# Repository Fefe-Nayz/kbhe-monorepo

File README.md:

# KBHE

KBHE is a Hall effect keyboard project packaged as one product monorepo: STM32 firmware, the Tauri desktop configurator, the 75HE KiCad PCB, and the mechanical 3D files live together with the documentation needed to build and maintain them.

**CAD: full assembly (v13)**

**Assembled 75% keyboard (pudding caps, RGB)**

## TIPE presentation (synoptic, report, part drawing)

Sourced materials for the TIPE deliverables: synoptic, English summary, part naming drawing, a short workbench video clip.

- [tipe-synoptique.pdf](assets/presentation/tipe-synoptique.pdf) — project synoptic
- [tipe-english-paper.pdf](assets/presentation/tipe-english-paper.pdf) — short English paper
- [tipe-drawing-part-labels.pdf](assets/presentation/tipe-drawing-part-labels.pdf) — drawing, part / reference labels
- [tipe-bench-clip.mp4](assets/presentation/tipe-bench-clip.mp4) — short bench / lab clip

## 75HE v1.0 main PCB (photographs)

| Top: switches + per-key RGB | Bottom: solder side (hand) |
| --- | --- |
|  |  |

## Final 75HE PCB (full board, KiCad 3D)

Renders of the main production board, exported from the KiCad project in `hardware/pcb/75he/Assets/`.

| Top (component side) | Bottom (solder side) |
| --- | --- |
|  |  |

## Prototyping: fabrication, plates, 3D prints

| Metal plate and 3D-printed top bezel | FDM: case half on the build plate | Printed set: top bezel, switch plate, bottom (75HE embossed) |
| --- | --- | --- |
|  |  |  |

## STM32 breakout, hall prototypes, and TIPE v0.1 bench setup

| STM32 test PCB: STLink + DFU silk | STM32: USB-C, DFU area (top) | STM32: bench, USB-C, DFU + flying wires |
| --- | --- | --- |
|  |  |  |

| 6-key Hall bench PCB | **TIPE Keyboard HE** v0.1 (CD74HC4067) — bench wiring | v0.1 Hall analog board **cabled to** STM32 breakout |
| --- | --- | --- |
|  |  |  |

## TIPE research bench and lab (wide stills)

| At the bench (1) | At the bench (2) | At the bench (3) |
| --- | --- | --- |
|  |  |  |

## First-time installation

Follow the instructions in [docs/firmware/INSTALLATION.md](docs/firmware/INSTALLATION.md) to flash the firmware for the first time using STM32CubeProgrammer.

<!-- ## First-time board programming (STM32CubeProgrammer, DFU)

The **first** time you program a **blank** board you need a Release build, the physical **DFU / FS** switch, **ROM DFU** over USB, and **STM32CubeProgrammer** to erase the chip and program the custom bootloader and application image. Ongoing updates use the Tauri app or the RAW HID tools instead.

**Step-by-step (French):** [docs/firmware/overview.md](docs/firmware/overview.md) — start at the section *Flash initial d'une carte neuve (bootloader custom)* (build → DFU connect → full erase → flash `kbhe_bootloader.hex` at `0x08000000` and `kbhe.hex` at `0x08010000` → normal boot → optional `raw_hid.py --flash` to finalize the updater). Related notes: [docs/firmware/raw_hid_usage.md](docs/firmware/raw_hid_usage.md), [docs/README.md](docs/README.md). -->

## Updating firmware

Follow the instructions in [docs/firmware/INSTALLATION.md](docs/firmware/INSTALLATION.md) to update the firmware using the Configurator app or STM32CubeProgrammer.

## Repository Layout

- `firmware/` - STM32F723 firmware, custom RAW HID bootloader, CMake toolchain and CubeMX-generated support files.
- `apps/configurator/` - Tauri desktop configurator for key settings, calibration, lighting, firmware flashing and app updates.
- `integrations/libhmk/` - pinned KBHE libhmk fork, portable RGB/HID protocol client, and reproducible upstream patch mirror.
- `hardware/pcb/75he/` - KiCad PCB project with project-local libraries, 3D models, documentation and legacy PCB revisions.
- `hardware/3d/` - mechanical source files and exported models. Large mechanical formats are tracked with Git LFS.
- `assets/presentation/` - TIPE PDFs (synoptic, English paper, part-label drawing) and a short workbench **.mp4** clip.
- `assets/cad/75he-mechanical/` - mechanical **CAD** stills: full assembly, shaded exploded stack, isometric, part-exploded **top / bottom / three-quarter** views.
- `assets/photos/` - real photos, grouped by topic: `product/`, `pcb-75he/`, `pcb-mcu-breakout/`, `prototypes/`, `fdm-fabrication/`, `tipe-lab/`, `app/`. No camera timestamps in file names: names describe **content**.
- `tools/`, `docs/`, `layouts/`, `data/` - as before.

## Firmware

```powershell
cmake --preset Release
cmake --build --preset Release
```

Artifacts are written to `build/Release/`. The CI also builds `Release-apponly` for app-only firmware packages. For a **first** flash of blank hardware, follow [docs/firmware/overview.md](docs/firmware/overview.md) (DFU, STM32CubeProgrammer) before relying on the app’s HID updater.

## Configurator

The desktop app communicates with the keyboard over RAW HID to handle keymap, performance, gamepad mode, calibration, the rotary encoder, lighting, and firmware updates. Example: **Keymap** for a 75% **ISO-FR** layout in dark UI.

```powershell
cd apps/configurator
bun install
bun run build
cd src-tauri
cargo check --locked
```

For a local installer build:

```powershell
cd apps/configurator
bun tauri build
```

## Releases

The monorepo uses explicit tag prefixes so the desktop app can distinguish app installers from firmware binaries:

- `firmware-vX.Y.Z` builds firmware artifacts and publishes them in a GitHub Release.
- `app-vX.Y.Z` builds the Tauri installer and publishes it in a GitHub Release.

The configurator checks these release streams from inside the app. App updates download and launch the published installer. Firmware updates download the latest firmware binary and flash it through the existing RAW HID update path.

## Working With 3D Assets

Install Git LFS before cloning or pushing mechanical changes:

```powershell
git lfs install
```

The current mechanical files are under `hardware/3d/current/`; older exports are kept under `hardware/3d/legacy/`.

## Mechanical CAD: exploded part views and overviews

Files live in `assets/cad/75he-mechanical/`. The **“parts”** set are consistent orientations of the decomposed case + plate; **“legacy”** older exports use different camera framing.

| Exploded: parts from top | Exploded: parts, bottom / rear | Exploded: three-quarter (right) |
| --- | --- | --- |
|  |  |  |

| All layers **stacked** (shade) | Full keyboard **3/4** (no case explode) | **Side elevation** (older export) | **Rear-left** isometric (older export) |
| --- | --- | --- | --- |
|  |  |  |  |

### Legacy KiCad prototypes (3D exports from the repo)

| 6-key Hall | MCU v1 | MCU v2 |
| --- | --- | --- |
|  |  |  |

## Current limitations - TODOs
- For transparent keycaps the space bar lacks leds on the sides
- For the enter key the led is colliding with the stabilizer which needs to be cut
- DFU switch should be hidden
- Wireless version
- Underglow
- Reversed mounted LEDs (single side pcb)
- Mountiing holes placements may need to be adjusted
- Try lowering pcb layer count without sacrificing noise performance
- Add support for libhmk
- Final touches on 3D models: adjust tolerances, raise the top case, adjust USB and switch hole position

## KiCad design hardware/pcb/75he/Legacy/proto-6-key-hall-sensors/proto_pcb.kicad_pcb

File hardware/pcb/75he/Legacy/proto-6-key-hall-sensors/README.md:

# Proto 6-Key Hall Sensors

Six-key prototype used to validate the hall-effect sensing approach only.

This board has no MCU and no keyboard logic. Its local `Library/` and `Docs/` folders are intentionally vendored so the project can be opened independently from the root PCB.

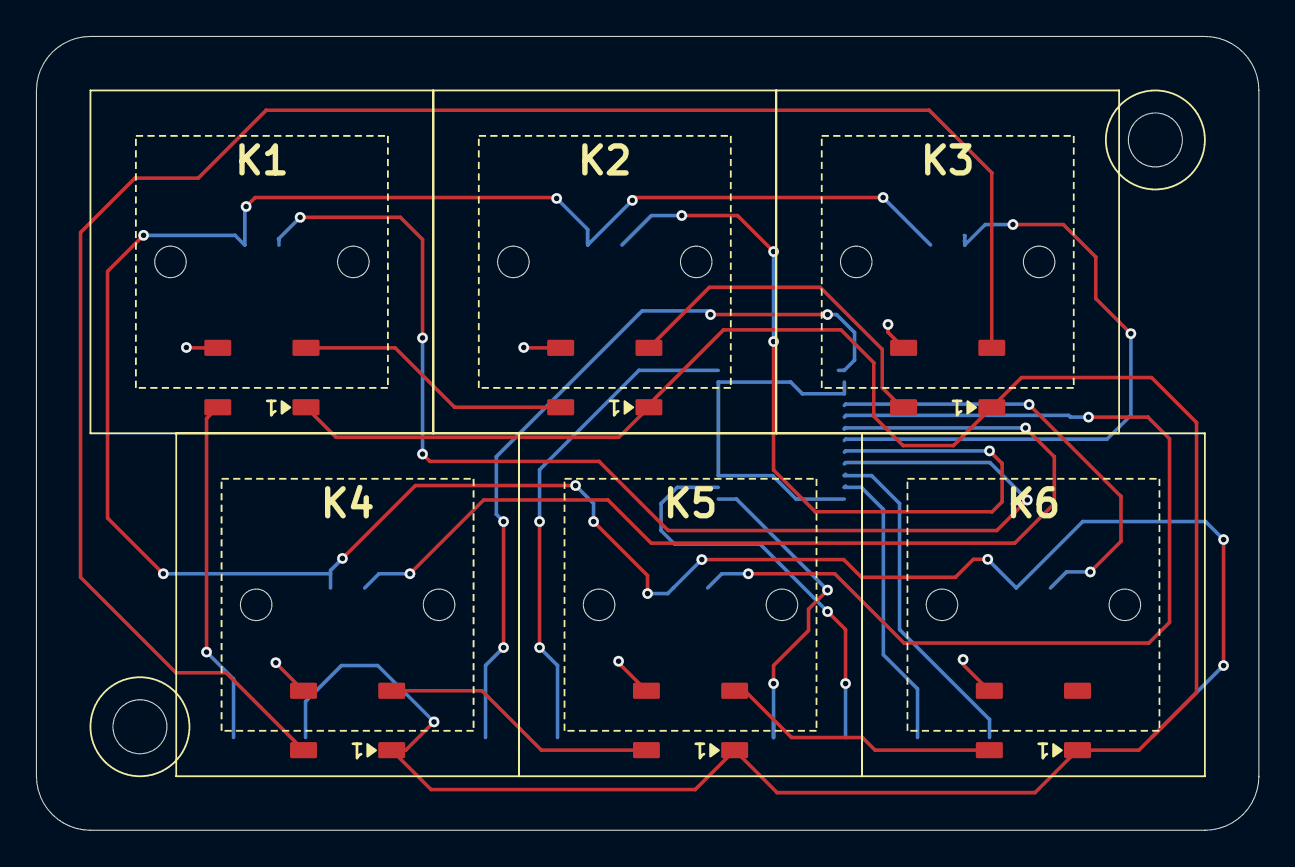
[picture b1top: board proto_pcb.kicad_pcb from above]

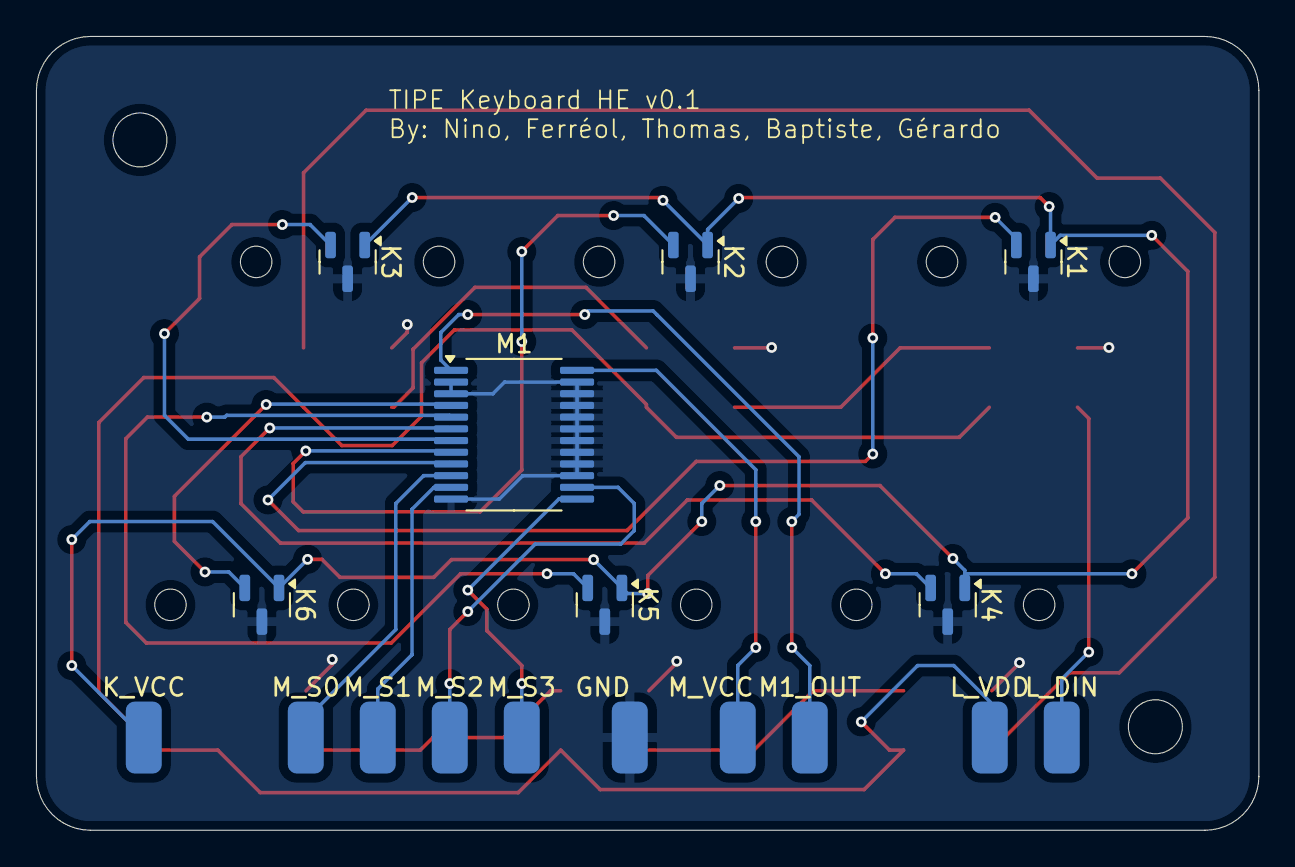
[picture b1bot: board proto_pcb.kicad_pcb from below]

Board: 2 copper layers, 67.9 x 44.1 mm, 23 parts (17 on the bottom side), 21 nets.

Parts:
GND: SolderWirePad_1x01_SMD_2x4mm
K1, K2, K3, K4, K5, K6: DRV5055A4QDBZR; SOT-23
K_VCC: SolderWirePad_1x01_SMD_2x4mm
L1, L2, L3, L4, L5, L6: XL-5050RGBC-2812B-S; LED_WS2812B_PLCC4_5.0x5.0mm_P3.2mm
L_DIN: SolderWirePad_1x01_SMD_2x4mm
L_VDD: SolderWirePad_1x01_SMD_2x4mm
M1: CD74HC4067SM96; SSOP-24_5.3x8.2mm_P0.65mm
M1_OUT: SolderWirePad_1x01_SMD_2x4mm
M_S0, M_S1, M_S2, M_S3: SolderWirePad_1x01_SMD_2x4mm
M_VCC: SolderWirePad_1x01_SMD_2x4mm

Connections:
GND: GND.10, K1.3 (GND), K2.3 (GND), K3.3 (GND), K4.3 (GND), K5.3 (GND), K6.3 (GND), L1.3 (VSS), L2.3 (VSS), L3.3 (VSS), L4.3 (VSS), L5.3 (VSS), L6.3 (VSS), M1.2 (I7), M1.3 (I6), M1.12 (GND), M1.15 (~E), M1.16 (I15), M1.17 (I14), M1.18 (I13), M1.19 (I12), M1.20 (I11), M1.21 (I10), M1.22 (I9), M1.23 (I8)
K1_OUT: K1.2 (OUT), M1.9 (I0)
K2_OUT: K2.2 (OUT), M1.8 (I1)
K3_OUT: K3.2 (OUT), M1.7 (I2)
K4_OUT: K4.2 (OUT), M1.6 (I3)
K5_OUT: K5.2 (OUT), M1.5 (I4)
K6_OUT: K6.2 (OUT), M1.4 (I5)
K_VCC: K1.1 (VCC), K2.1 (VCC), K3.1 (VCC), K4.1 (VCC), K5.1 (VCC), K6.1 (VCC), K_VCC.8
L_DIN: L1.4 (DIN), L_DIN.5
L_VDD: L1.1 (VDD), L2.1 (VDD), L3.1 (VDD), L4.1 (VDD), L5.1 (VDD), L6.1 (VDD), L_VDD.9
M1_OUT: M1.1 (COM), M1_OUT.6
M_S0: M1.10 (S0), M_S0.1
M_S1: M1.11 (S1), M_S1.2
M_S2: M1.14 (S2), M_S2.3
M_S3: M1.13 (S3), M_S3.4
M_VCC: M1.24 (VCC), M_VCC.7
unnamed: L1.2 (DOUT), L2.4 (DIN)
unnamed: L2.2 (DOUT), L3.4 (DIN)
unnamed: L3.2 (DOUT), L4.4 (DIN)
unnamed: L4.2 (DOUT), L5.4 (DIN)
unnamed: L5.2 (DOUT), L6.4 (DIN)

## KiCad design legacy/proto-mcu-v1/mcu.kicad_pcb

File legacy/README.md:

# Legacy PCB Revisions

This folder keeps older KiCad project revisions as source-only archives.

Generated outputs, backups, fabrication packages, render exports, footprint caches, and local KiCad UI state were intentionally removed. The projects keep their KiCad sources and required local libraries, with external 3D model references rewritten to repository-local paths where available.

Each legacy project keeps KiCad project files at its root and stores project-local libraries under `Library/`:

- `Library/Footprints`
- `Library/Symbols`
- `Library/3D`

Projects:

- `mcu-2025-11-18`: MCU board revision from `hall-effect-keyboard/mcu-final/mcu-2025-11-18_230059`.
- `mcu-2025-11-18-04f0a440`: MCU board revision from the downloaded `hall-effect-keyboard-04f0a440...` archive.
- `proto-pcb`: prototype PCB revisions from `hall-effect-keyboard/proto_pcb`.

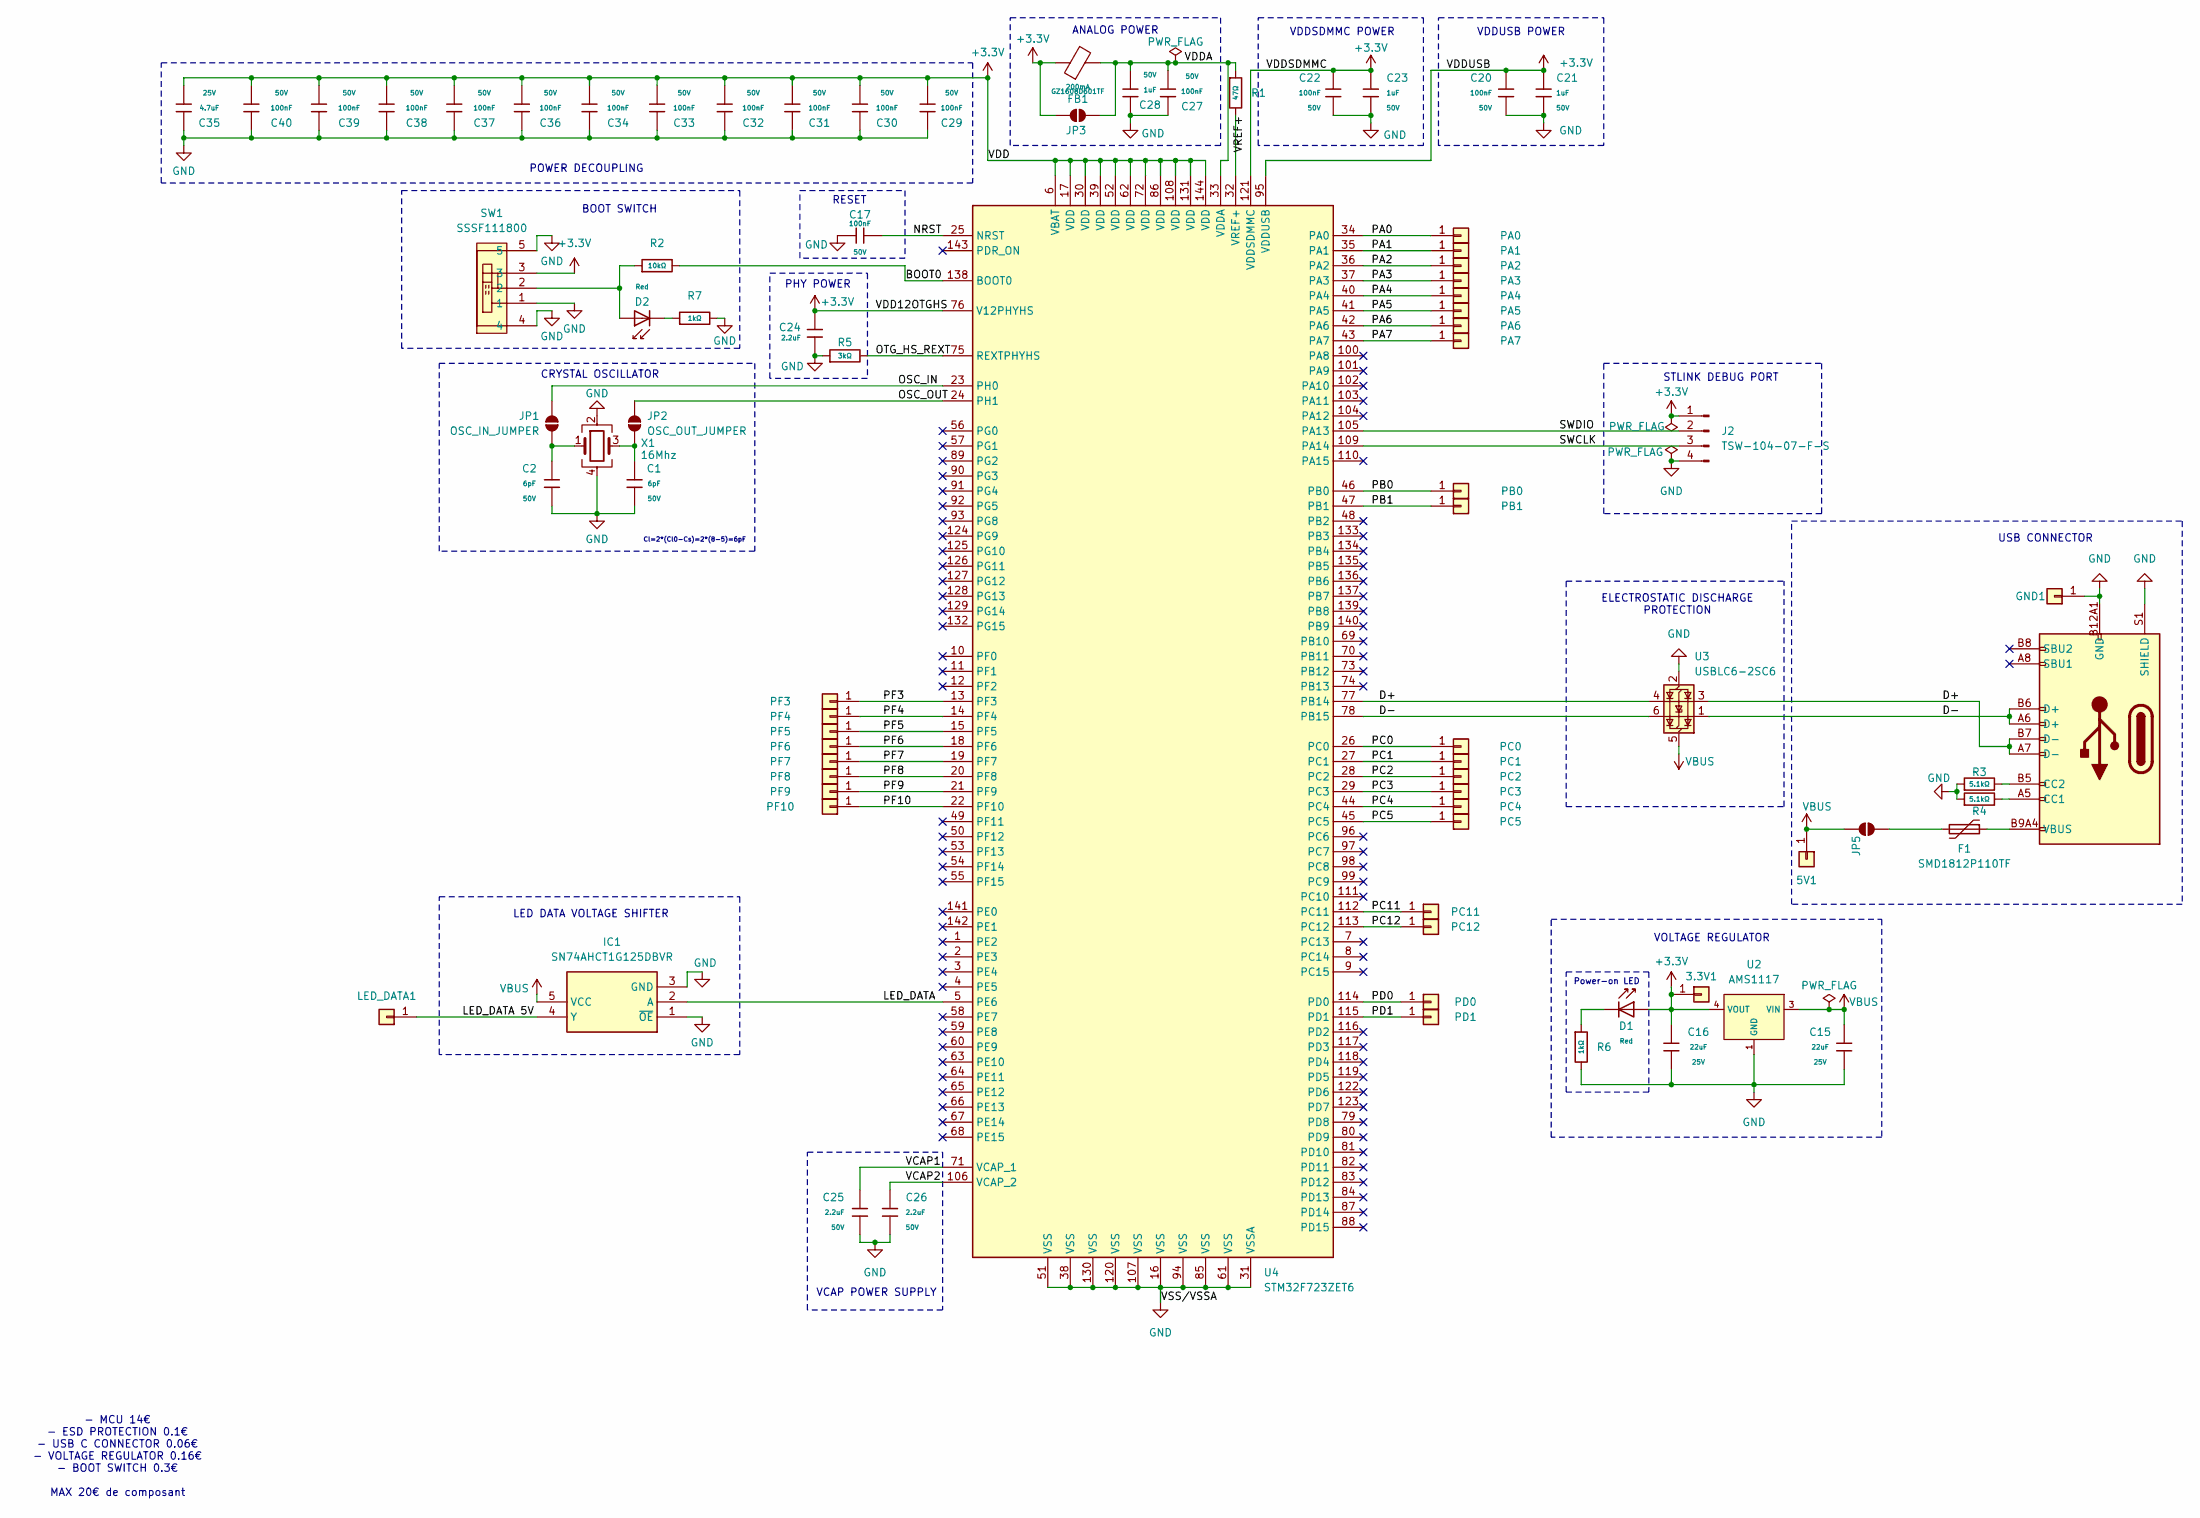
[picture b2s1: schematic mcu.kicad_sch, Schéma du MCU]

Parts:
3.3V1, 5V1: Conn_01x01; SolderWirePad_1x01_SMD_2x4mm
C1, C2: 6pF; C_0603; Voltage Rated 50V; Tolerance ±5%; Part CL10C100JB8NNNC; LCSC C1634
C15, C16: 22uF; C_0805; Voltage Rated 25V; Tolerance ±20%; Part CL21A226MAQNNNE; LCSC C45783
C17, C20, C22, C27, C29, C30, C31, C32, C33, C34, C36, C37, C38, C39, C40: 100nF; C_0603; Voltage Rated 50V; Tolerance ±10%; Part CC0603KRX7R9BB104; LCSC C14663
C21, C23, C28: 1uF; C_0805; Voltage Rated 50V; Tolerance ±10%; Part CL21B105KBFNNNE; LCSC C28323
C24, C25, C26: 2.2uF; C_0805; Voltage Rated 50V; Tolerance ±10%; Part CL21A225KBQNNNE; LCSC C377773
C35: 4.7uF; C_0805; Voltage Rated 25V; Tolerance ±10%; Part CL21A475KAQNNNE; LCSC C1779
D1, D2: Red; D_0603; Part KT-0603R; LCSC C2286
F1: SMD1812P110TF; Fuse_1812_4532Metric; LCSC C3102
FB1: GZ1608D601TF; FB_0603; Current Rating 200mA; Tolerance ±25%; Part GZ1608D601TF; LCSC C1002
GND1: Conn_01x01; SolderWirePad_1x01_SMD_2x4mm
IC1: SN74AHCT1G125DBVR; SOT95P280X145-5N; Manufacturer_Part_Number SN74AHCT1G125DBVR; Mouser Part Number 595-SNAHCT1G125DBVR
J1: Connector, USB-TYPE-C-16P; TYPE-C-SMD_HX-TYPE-C-16PIN; LCSC C2927039
J2: TSW-104-07-F-S; PinHeader_1x04_P2.54mm_Vertical; LCSC C3329057
JP1: OSC_IN_JUMPER; SolderJumper-2_P1.3mm_Open_RoundedPad1.0x1.5mm
JP2: OSC_OUT_JUMPER; SolderJumper-2_P1.3mm_Open_RoundedPad1.0x1.5mm
JP3: FERRITE_IN_JUMP; SolderJumper-2_P1.3mm_Open_RoundedPad1.0x1.5mm
JP5: VBUS_JP; SolderJumper-2_P1.3mm_Open_RoundedPad1.0x1.5mm
LED_DATA1: Conn_01x01; SolderWirePad_1x01_SMD_2x4mm
PA0, PA1, PA2, PA3, PA4, PA5, PA6, PA7: Conn_01x01; SolderWirePad_1x01_SMD_2x4mm
PB0, PB1: Conn_01x01; SolderWirePad_1x01_SMD_2x4mm
PC0, PC1, PC2, PC3, PC4, PC5, PC11, PC12: Conn_01x01; SolderWirePad_1x01_SMD_2x4mm
PD0, PD1: Conn_01x01; SolderWirePad_1x01_SMD_2x4mm
PF3, PF4, PF5, PF6, PF7, PF8, PF9, PF10: Conn_01x01; SolderWirePad_1x01_SMD_2x4mm
R1: 47Ω; R_0402; Overload Voltage (Max) 50V; Tolerance ±1%; Part 0402WGF470JTCE; LCSC C25118
R2: 10kΩ; R_0402; Overload Voltage (Max) 50V; Tolerance ±1%; Part 0402WGF1002TCE; LCSC C25744
R3, R4: 5.1kΩ; R_0402; Overload Voltage (Max) 50V; Tolerance ±1%; Part 0402WGF5101TCE; LCSC C25905
R5: 3kΩ; R_0805; Overload Voltage (Max) 150V; Tolerance ±1%; Part 0805W8F3001T5E; LCSC C17661
R6, R7: 1kΩ; R_0402; Overload Voltage (Max) 50V; Tolerance ±1%; Part 0402WGF1001TCE; LCSC C11702
SW1: SSSF111800; SW-TH_SSSF111800; LCSC Part C97450
U2: AMS1117; SOT-223-3_L6.5-W3.4-P2.30-LS7.0-BR; Output Voltage 3.3V; Dropout Voltage 1.3V@(800mA); Part AMS1117-3.3; LCSC C6186
U3: USBLC6-2SC6; SOT-23-6; LCSC C7519
U4: STM32F723ZET6; LQFP-144_20x20mm_P0.5mm; LCSC C1340305
X1: 16Mhz; Crystal_SMD_2520-4Pin_2.5x2.0mm; LCSC C280836

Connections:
+3.3V: 3.3V1.1, C16.1, C20.1, C21.2, C22.1, C23.2, C24.1, C29.1, C30.1, C31.1, C32.1, C33.1, C34.1, C35.1, C36.1, C37.1, C38.1, C39.1, C40.1, D1.2, FB1.1, J2.1, JP3.1 (A), SW1.3, U2.2 (VOUT), U2.4 (VOUT), U4.6 (VBAT), U4.17 (VDD), U4.30 (VDD), U4.39 (VDD), U4.52 (VDD), U4.62 (VDD), U4.72 (VDD), U4.76 (V12PHYHS), U4.86 (VDD), U4.95 (VDDUSB), U4.108 (VDD), U4.121 (VDDSDMMC), U4.131 (VDD), U4.144 (VDD)
/BOOT0: R2.2, U4.138 (BOOT0)
/D+: J1.A7 (D-), J1.B7 (D-), U3.3 (I/O2), U3.4 (I/O2), U4.77 (PB14)
/D-: J1.A6 (D+), J1.B6 (D+), U3.1 (I/O1), U3.6 (I/O1), U4.78 (PB15)
/LED_DATA: IC1.2 (A), U4.5 (PE6)
/LED_DATA 5V: IC1.4 (Y), LED_DATA1.1
/NRST: C17.1, U4.25 (NRST)
/OSC_IN: JP1.1 (A), U4.23 (PH0)
/OSC_OUT: JP2.2 (B), U4.24 (PH1)
/OTG_HS_REXT: R5.2, U4.75 (REXTPHYHS)
/PA0: PA0.1, U4.34 (PA0)
/PA1: PA1.1, U4.35 (PA1)
/PA2: PA2.1, U4.36 (PA2)
/PA3: PA3.1, U4.37 (PA3)
/PA4: PA4.1, U4.40 (PA4)
/PA5: PA5.1, U4.41 (PA5)
/PA6: PA6.1, U4.42 (PA6)
/PA7: PA7.1, U4.43 (PA7)
/PB0: PB0.1, U4.46 (PB0)
/PB1: PB1.1, U4.47 (PB1)
/PC0: PC0.1, U4.26 (PC0)
/PC1: PC1.1, U4.27 (PC1)
/PC2: PC2.1, U4.28 (PC2)
/PC3: PC3.1, U4.29 (PC3)
/PC4: PC4.1, U4.44 (PC4)
/PC5: PC5.1, U4.45 (PC5)
/PC11: PC11.1, U4.112 (PC11)
/PC12: PC12.1, U4.113 (PC12)
/PD0: PD0.1, U4.114 (PD0)
/PD1: PD1.1, U4.115 (PD1)
/PF3: PF3.1, U4.13 (PF3)
/PF4: PF4.1, U4.14 (PF4)
/PF5: PF5.1, U4.15 (PF5)
/PF6: PF6.1, U4.18 (PF6)
/PF7: PF7.1, U4.19 (PF7)
/PF8: PF8.1, U4.20 (PF8)
/PF9: PF9.1, U4.21 (PF9)
/PF10: PF10.1, U4.22 (PF10)
/SWCLK: J2.3, U4.109 (PA14)
/SWDIO: J2.2, U4.105 (PA13)
/VCAP1: C25.2, U4.71 (VCAP_1)
/VCAP2: C26.2, U4.106 (VCAP_2)
/VDDA: C27.1, C28.1, FB1.2, JP3.2 (B), R1.1, U4.33 (VDDA)
/VREF+: R1.2, U4.32 (VREF+)
GND: C1.2, C2.2, C15.2, C16.2, C17.2, C20.2, C21.1, C22.2, C23.1, C24.2, C25.1, C26.1, C27.2, C28.2, C29.2, C30.2, C31.2, C32.2, C33.2, C34.2, C35.2, C36.2, C37.2, C38.2, C39.2, C40.2, GND1.1, IC1.1 (~OE), IC1.3 (GND), J1.A12B1 (GND), J1.B12A1 (GND), J1.S1 (SHIELD), J2.4, R3.1, R4.1, R5.1, R6.2, R7.2, SW1.1, SW1.4, SW1.5, U2.1 (GND), U3.2 (GND), U4.16 (VSS), U4.31 (VSSA), U4.38 (VSS), U4.51 (VSS), U4.61 (VSS), U4.85 (VSS), U4.94 (VSS), U4.107 (VSS), U4.120 (VSS), U4.130 (VSS), X1.2, X1.4
unnamed: D1.1, R6.1
unnamed: D2.1, R7.1
unnamed: D2.2, R2.1, SW1.2
unnamed: F1.1, J1.A9B4 (VBUS), J1.B9A4 (VBUS)
unnamed: J1.A5 (CC1), R4.2
unnamed: J1.B5 (CC2), R3.2
unnamed: C2.1, JP1.2 (B), X1.1
unnamed: C1.1, JP2.1 (A), X1.3
unnamed: F1.2, JP5.2 (B)
VBUS: 5V1.1, C15.1, IC1.5 (VCC), JP5.1 (A), U2.3 (VIN), U3.5 (VBUS)

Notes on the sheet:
STLINK DEBUG PORT
VDDSDMMC POWER
PHY POWER
LED DATA VOLTAGE SHIFTER
USB CONNECTOR
VCAP POWER SUPPLY
ELECTROSTATIC DISCHARGE PROTECTION
VOLTAGE REGULATOR
POWER DECOUPLING
Cl=2*(Cl0-Cs)=2*(8-5)=6pF
Power-on LED
- MCU 14€ - ESD PROTECTION 0.1€ - USB C CONNECTOR 0.06€ - VOLTAGE REGULATOR 0.16€ - BOOT SWITCH 0.3€ MAX 20€ de composant
BOOT SWITCH
CRYSTAL OSCILLATOR
ANALOG POWER
RESET
VDDUSB POWER

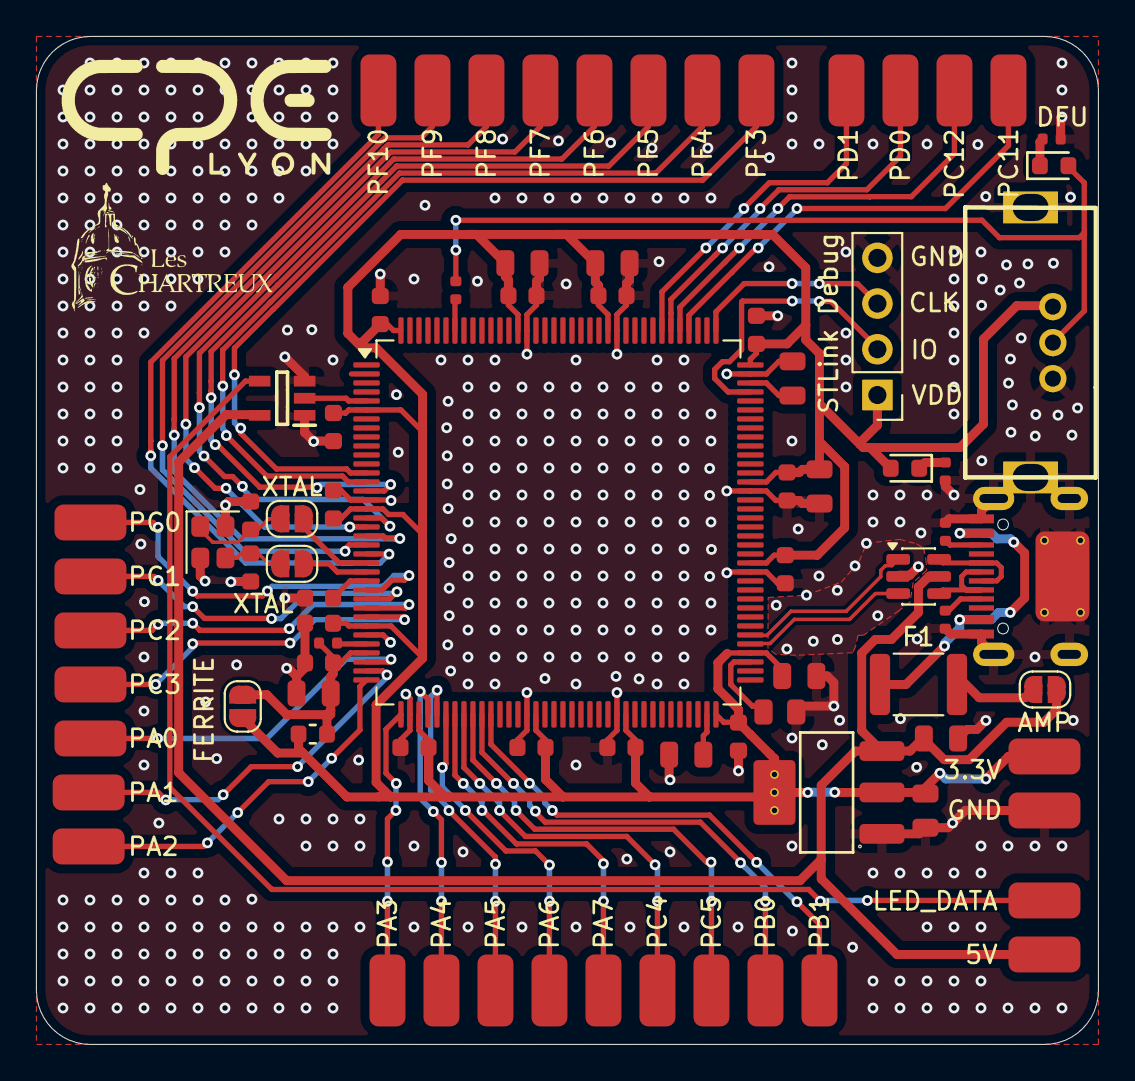
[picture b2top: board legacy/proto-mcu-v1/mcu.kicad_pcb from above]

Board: 2 copper layers, 59.0 x 56.0 mm, 81 parts (0 on the bottom side), 55 nets.

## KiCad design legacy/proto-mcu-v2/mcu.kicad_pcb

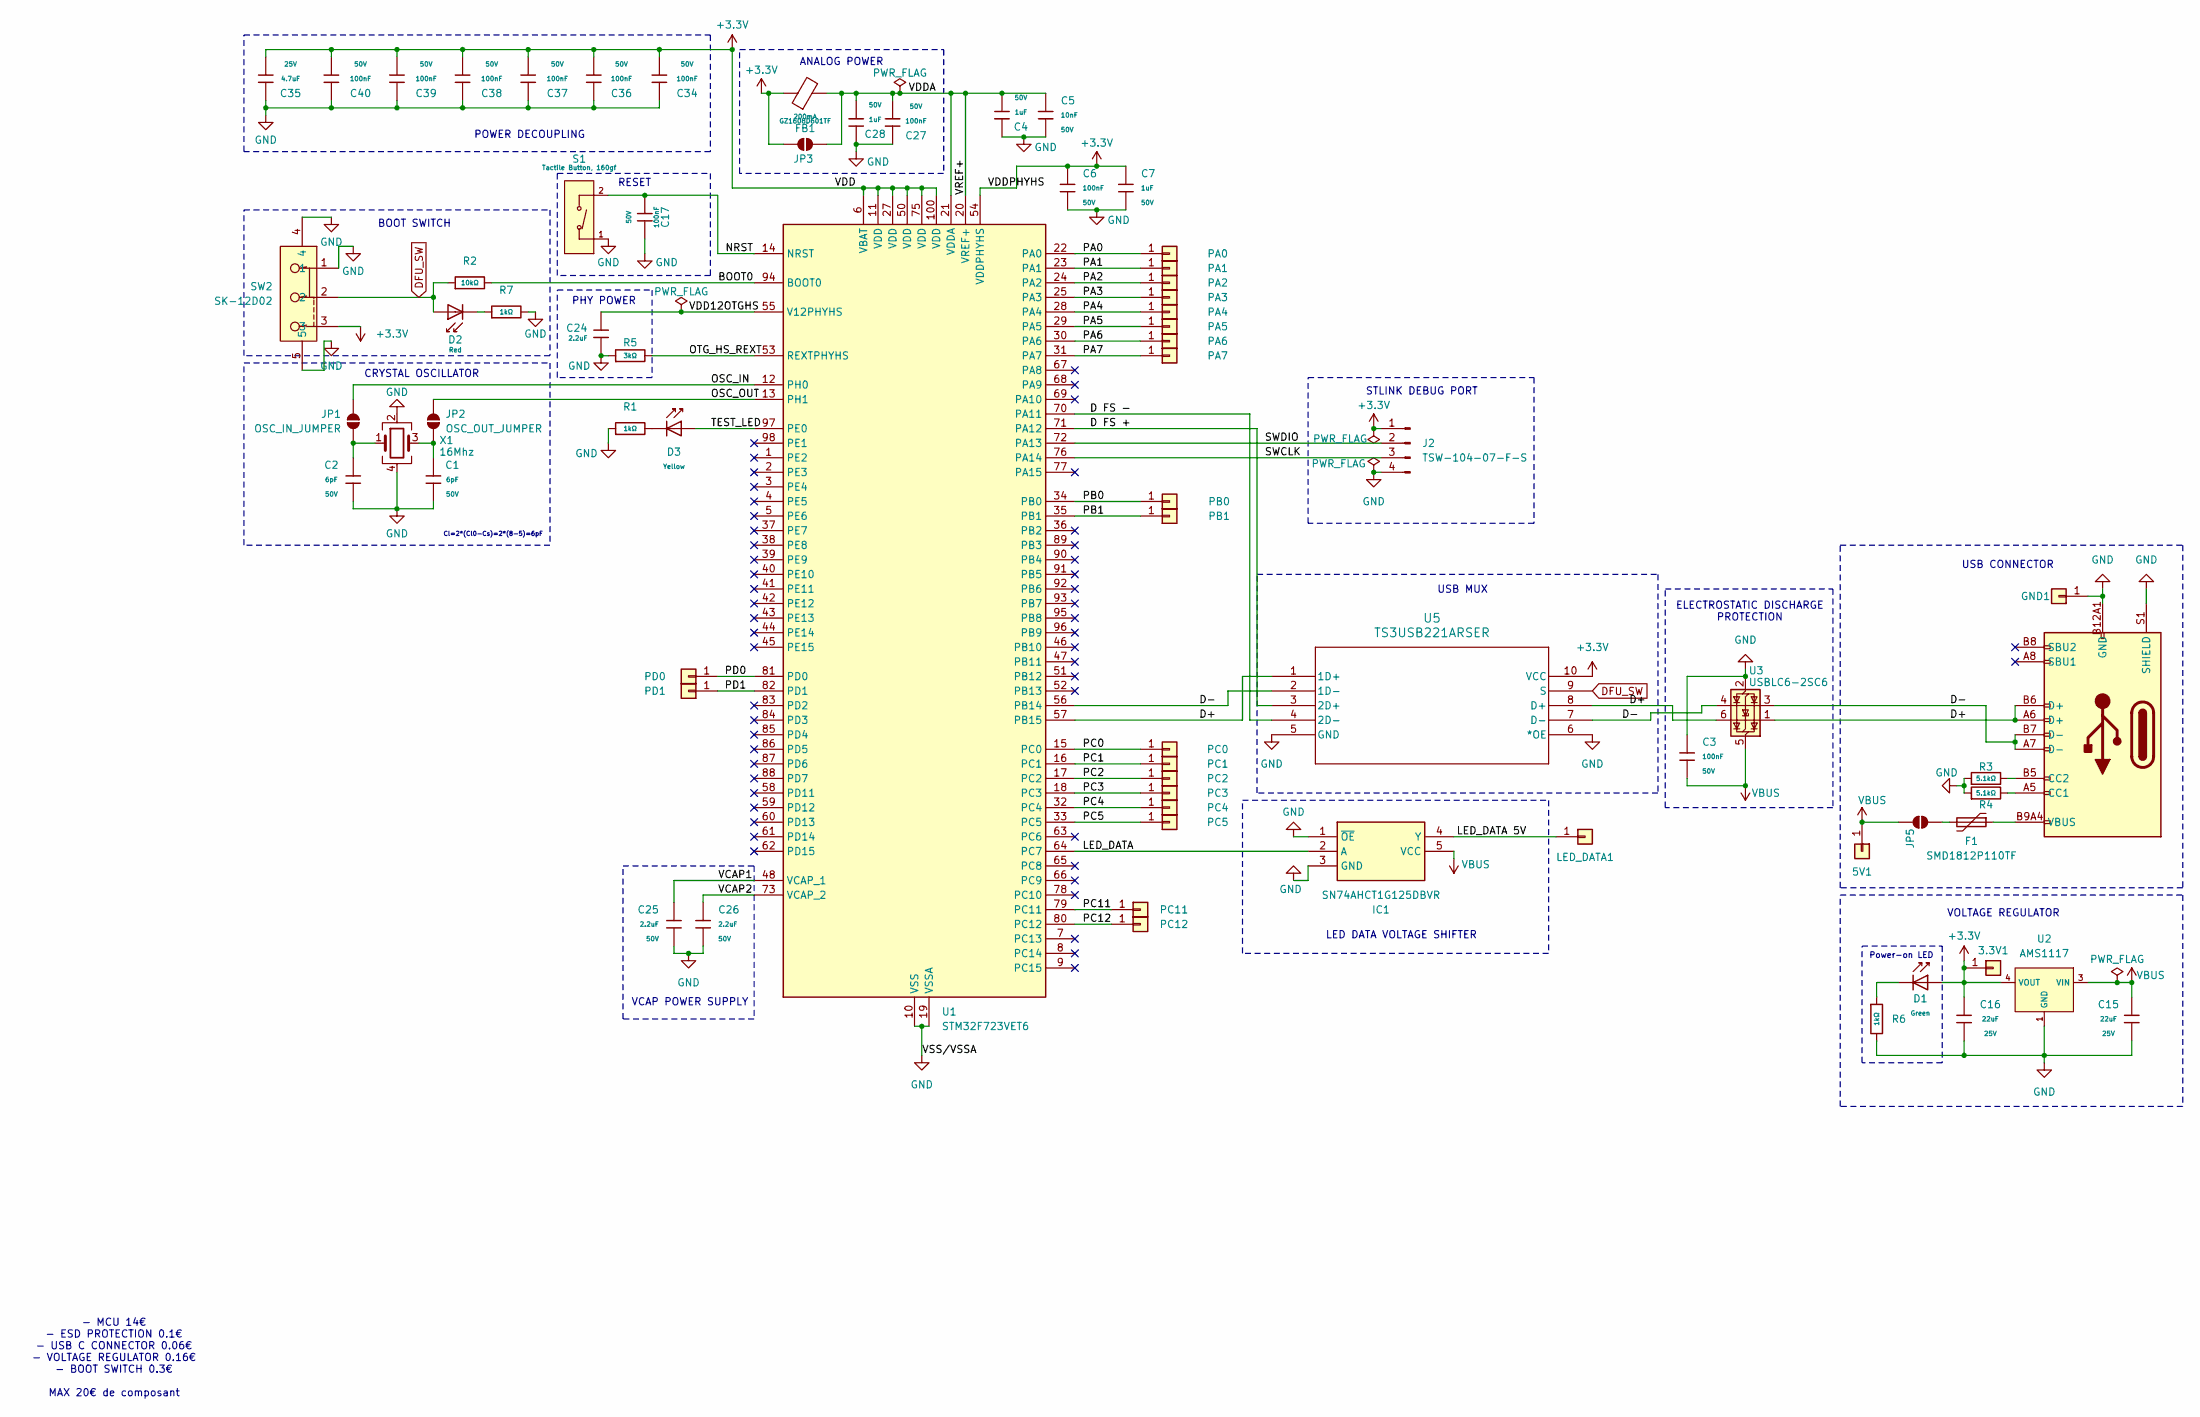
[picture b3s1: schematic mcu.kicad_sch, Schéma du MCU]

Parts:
3.3V1, 5V1: Conn_01x01; SolderWirePad_1x01_SMD_2x4mm
C1, C2: 6pF; C_0603; Voltage Rated 50V; Tolerance ±5%; Part CL10C100JB8NNNC; LCSC C1634
C3, C6, C17, C27, C34, C36, C37, C38, C39, C40: 100nF; C_0603; Voltage Rated 50V; Tolerance ±10%; Part CC0603KRX7R9BB104; LCSC C14663
C4, C7, C28: 1uF; C_0805; Voltage Rated 50V; Tolerance ±10%; Part CL21B105KBFNNNE; LCSC C28323
C5: 10nF; C_0402; Voltage Rated 50V; Tolerance ±10%; Part CL05B103KB5NNNC; LCSC C15195
C15, C16: 22uF; C_0805; Voltage Rated 25V; Tolerance ±20%; Part CL21A226MAQNNNE; LCSC C45783
C24, C25, C26: 2.2uF; C_0805; Voltage Rated 50V; Tolerance ±10%; Part CL21A225KBQNNNE; LCSC C377773
C35: 4.7uF; C_0805; Voltage Rated 25V; Tolerance ±10%; Part CL21A475KAQNNNE; LCSC C1779
D1: Green; D_0805; Part KT-0805G; LCSC C2297
D2: Red; D_0603; Part KT-0603R; LCSC C2286
D3: Yellow; D_0603; Forward Voltage (VF) 1.6V~2.6V; Part NCD0603Y2; LCSC C89811
F1: SMD1812P110TF; Fuse_1812_4532Metric; LCSC C3102
FB1: GZ1608D601TF; FB_0603; Current Rating 200mA; Tolerance ±25%; Part GZ1608D601TF; LCSC C1002
GND1: Conn_01x01; SolderWirePad_1x01_SMD_2x4mm
IC1: SN74AHCT1G125DBVR; SOT95P280X145-5N; Manufacturer_Part_Number SN74AHCT1G125DBVR; Mouser Part Number 595-SNAHCT1G125DBVR
J1: Connector, USB-TYPE-C-16P; TYPE-C-SMD_HX-TYPE-C-16PIN; LCSC C2927039
J2: TSW-104-07-F-S; PinHeader_1x04_P2.54mm_Vertical; LCSC C3329057
JP1: OSC_IN_JUMPER; SolderJumper-2_P1.3mm_Open_RoundedPad1.0x1.5mm
JP2: OSC_OUT_JUMPER; SolderJumper-2_P1.3mm_Open_RoundedPad1.0x1.5mm
JP3: FERRITE_IN_JUMP; SolderJumper-2_P1.3mm_Open_RoundedPad1.0x1.5mm
JP5: VBUS_JP; SolderJumper-2_P1.3mm_Open_RoundedPad1.0x1.5mm
LED_DATA1: Conn_01x01; SolderWirePad_1x01_SMD_2x4mm
PA0, PA1, PA2, PA3, PA4, PA5, PA6, PA7: Conn_01x01; SolderWirePad_1x01_SMD_2x4mm
PB0, PB1: Conn_01x01; SolderWirePad_1x01_SMD_2x4mm
PC0, PC1, PC2, PC3, PC4, PC5, PC11, PC12: Conn_01x01; SolderWirePad_1x01_SMD_2x4mm
PD0, PD1: Conn_01x01; SolderWirePad_1x01_SMD_2x4mm
R1, R6, R7: 1kΩ; R_0402; Overload Voltage (Max) 50V; Tolerance ±1%; Part 0402WGF1001TCE; LCSC C11702
R2: 10kΩ; R_0402; Overload Voltage (Max) 50V; Tolerance ±1%; Part 0402WGF1002TCE; LCSC C25744
R3, R4: 5.1kΩ; R_0402; Overload Voltage (Max) 50V; Tolerance ±1%; Part 0402WGF5101TCE; LCSC C25905
R5: 3kΩ; R_0805; Overload Voltage (Max) 150V; Tolerance ±1%; Part 0805W8F3001T5E; LCSC C17661
S1: Tactile Button, 160gf; SW_TS-1088-AR02016; Voltage Rating (Dc) 12V; Part TS-1088-AR02016; LCSC C720477
SW2: SK-12D02; SW-TH_SK-12D02VG3; LCSC Part C131374
U1: STM32F723VET6; LQFP-100_14x14mm_P0.5mm; LCSC C5270022
U2: AMS1117; SOT-223-3_L6.5-W3.4-P2.30-LS7.0-BR; Output Voltage 3.3V; Dropout Voltage 1.3V@(800mA); Part AMS1117-3.3; LCSC C6186
U3: USBLC6-2SC6; SOT-23-6; LCSC C7519
U5: TS3USB221ARSER; RSE10
X1: 16Mhz; Crystal_SMD_2520-4Pin_2.5x2.0mm; LCSC C280836

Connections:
+3.3V: 3.3V1.1, C6.1, C7.1, C16.1, C34.1, C35.1, C36.1, C37.1, C38.1, C39.1, C40.1, D1.2, FB1.1, J2.1, JP3.1 (A), SW2.3, U1.6 (VBAT), U1.11 (VDD), U1.27 (VDD), U1.50 (VDD), U1.54 (VDDPHYHS), U1.75 (VDD), U1.100 (VDD), U2.2 (VOUT), U2.4 (VOUT), U5.10 (VCC)
/BOOT0: R2.2, U1.94 (BOOT0)
/D FS +: U1.71 (PA12), U5.3 (2D+)
/D FS -: U1.70 (PA11), U5.4 (2D-)
/D+: J1.A6 (D+), J1.B6 (D+), U1.57 (PB15), U3.1 (I/O1), U3.6 (I/O1), U5.1 (1D+), U5.8 (D+)
/D-: J1.A7 (D-), J1.B7 (D-), U1.56 (PB14), U3.3 (I/O2), U3.4 (I/O2), U5.2 (1D-), U5.7 (D-)
/LED_DATA: IC1.2 (A), U1.64 (PC7)
/LED_DATA 5V: IC1.4 (Y), LED_DATA1.1
/NRST: C17.2, S1.2 (B), U1.14 (NRST)
/OSC_IN: JP1.1 (A), U1.12 (PH0)
/OSC_OUT: JP2.2 (B), U1.13 (PH1)
/OTG_HS_REXT: R5.2, U1.53 (REXTPHYHS)
/PA0: PA0.1, U1.22 (PA0)
/PA1: PA1.1, U1.23 (PA1)
/PA2: PA2.1, U1.24 (PA2)
/PA3: PA3.1, U1.25 (PA3)
/PA4: PA4.1, U1.28 (PA4)
/PA5: PA5.1, U1.29 (PA5)
/PA6: PA6.1, U1.30 (PA6)
/PA7: PA7.1, U1.31 (PA7)
/PB0: PB0.1, U1.34 (PB0)
/PB1: PB1.1, U1.35 (PB1)
/PC0: PC0.1, U1.15 (PC0)
/PC1: PC1.1, U1.16 (PC1)
/PC2: PC2.1, U1.17 (PC2)
/PC3: PC3.1, U1.18 (PC3)
/PC4: PC4.1, U1.32 (PC4)
/PC5: PC5.1, U1.33 (PC5)
/PC11: PC11.1, U1.79 (PC11)
/PC12: PC12.1, U1.80 (PC12)
/PD0: PD0.1, U1.81 (PD0)
/PD1: PD1.1, U1.82 (PD1)
/SWCLK: J2.3, U1.76 (PA14)
/SWDIO: J2.2, U1.72 (PA13)
/TEST_LED: D3.2, U1.97 (PE0)
/VCAP1: C25.2, U1.48 (VCAP_1)
/VCAP2: C26.2, U1.73 (VCAP_2)
/VDD12OTGHS: C24.1, U1.55 (V12PHYHS)
/VDDA: C4.1, C5.1, C27.1, C28.1, FB1.2, JP3.2 (B), U1.20 (VREF+), U1.21 (VDDA)
DFU_SW: D2.2, R2.1, SW2.2, U5.9 (S)
GND: C1.2, C2.2, C3.1, C4.2, C5.2, C6.2, C7.2, C15.2, C16.2, C17.1, C24.2, C25.1, C26.1, C27.2, C28.2, C34.2, C35.2, C36.2, C37.2, C38.2, C39.2, C40.2, GND1.1, IC1.1 (~OE), IC1.3 (GND), J1.A12B1 (GND), J1.B12A1 (GND), J1.S1 (SHIELD), J2.4, R1.1, R3.1, R4.1, R5.1, R6.2, R7.2, S1.1 (A), SW2.1, SW2.4, SW2.5, U1.10 (VSS), U1.19 (VSSA), U1.26 (VSS), U1.49 (VSS), U1.74 (VSS), U1.99 (VSS), U2.1 (GND), U3.2 (GND), U5.5 (GND), U5.6 (*OE), X1.2, X1.4
unnamed: D1.1, R6.1
unnamed: D2.1, R7.1
unnamed: D3.1, R1.2
unnamed: F1.1, J1.A9B4 (VBUS), J1.B9A4 (VBUS)
unnamed: J1.A5 (CC1), R4.2
unnamed: J1.B5 (CC2), R3.2
unnamed: C2.1, JP1.2 (B), X1.1
unnamed: C1.1, JP2.1 (A), X1.3
unnamed: F1.2, JP5.2 (B)
VBUS: 5V1.1, C3.2, C15.1, IC1.5 (VCC), JP5.1 (A), U2.3 (VIN), U3.5 (VBUS)

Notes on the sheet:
STLINK DEBUG PORT
PHY POWER
USB CONNECTOR
LED DATA VOLTAGE SHIFTER
VCAP POWER SUPPLY
ELECTROSTATIC DISCHARGE PROTECTION
VOLTAGE REGULATOR
POWER DECOUPLING
USB MUX
Cl=2*(Cl0-Cs)=2*(8-5)=6pF
Power-on LED
- MCU 14€ - ESD PROTECTION 0.1€ - USB C CONNECTOR 0.06€ - VOLTAGE REGULATOR 0.16€ - BOOT SWITCH 0.3€ MAX 20€ de composant
BOOT SWITCH
CRYSTAL OSCILLATOR
ANALOG POWER
RESET

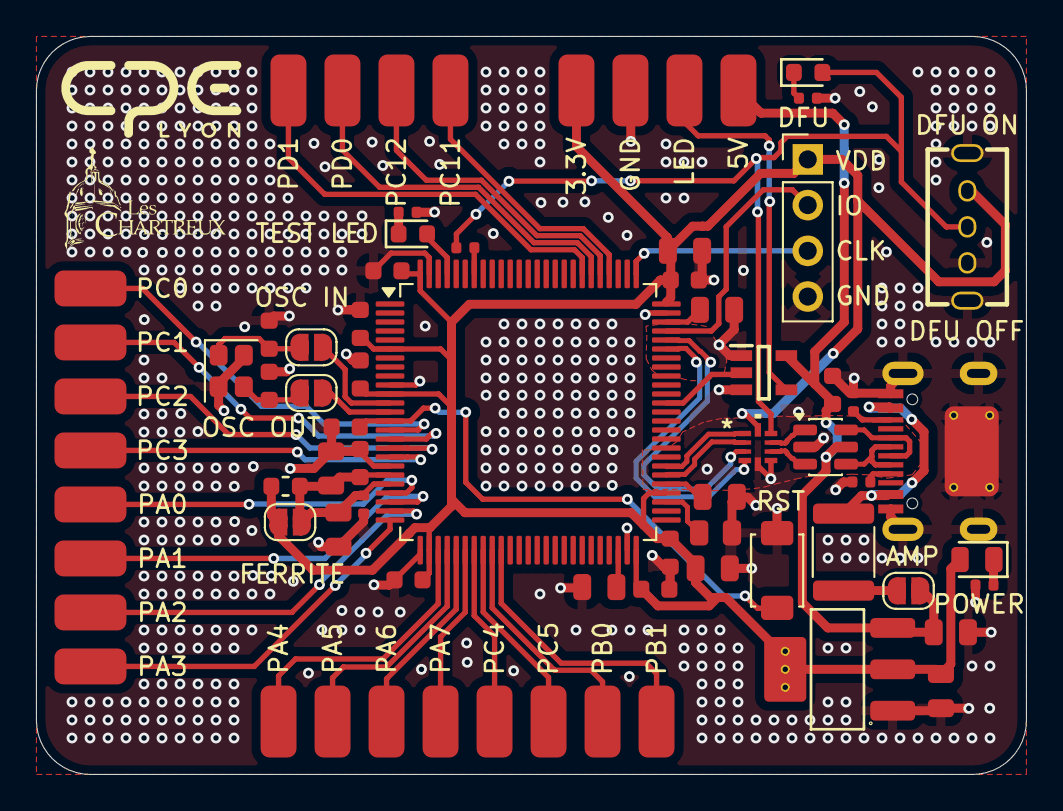
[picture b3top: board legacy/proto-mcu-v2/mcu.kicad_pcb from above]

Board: 2 copper layers, 55.0 x 41.0 mm, 72 parts (0 on the bottom side), 51 nets.

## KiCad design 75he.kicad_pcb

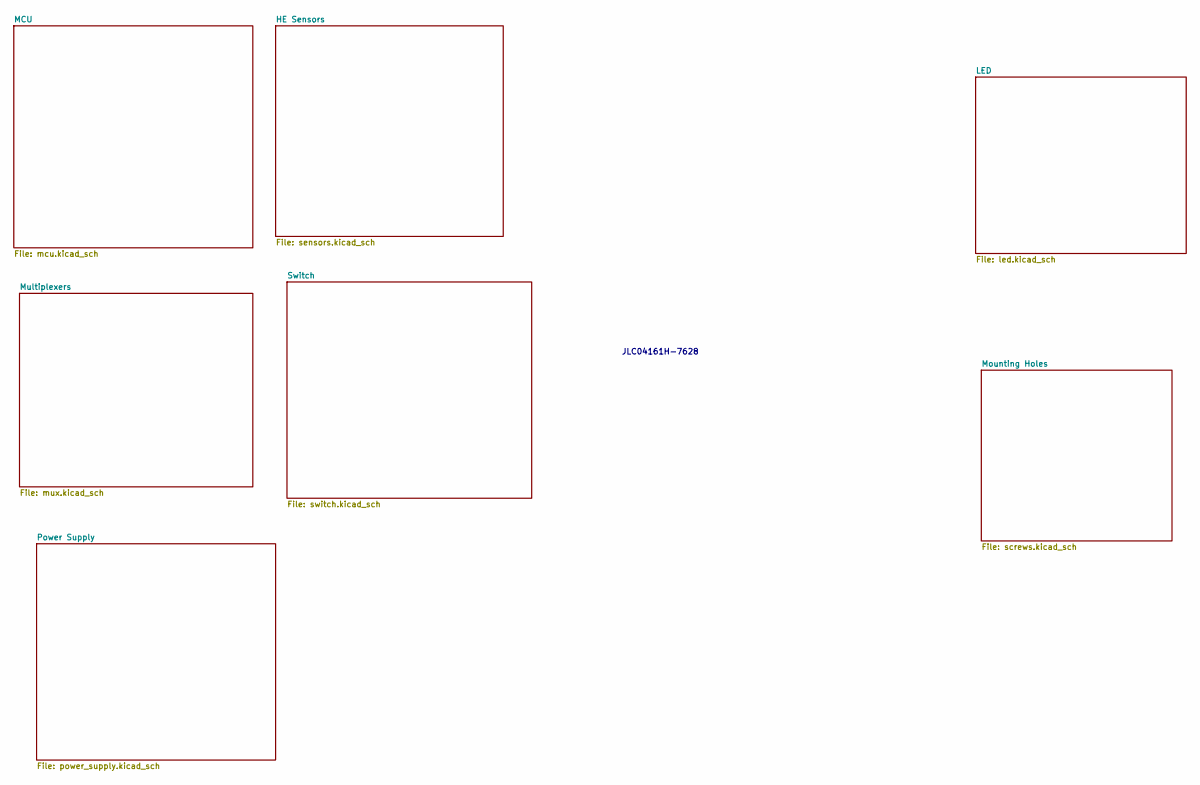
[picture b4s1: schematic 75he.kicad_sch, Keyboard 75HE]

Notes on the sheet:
JLC04161H-7628
